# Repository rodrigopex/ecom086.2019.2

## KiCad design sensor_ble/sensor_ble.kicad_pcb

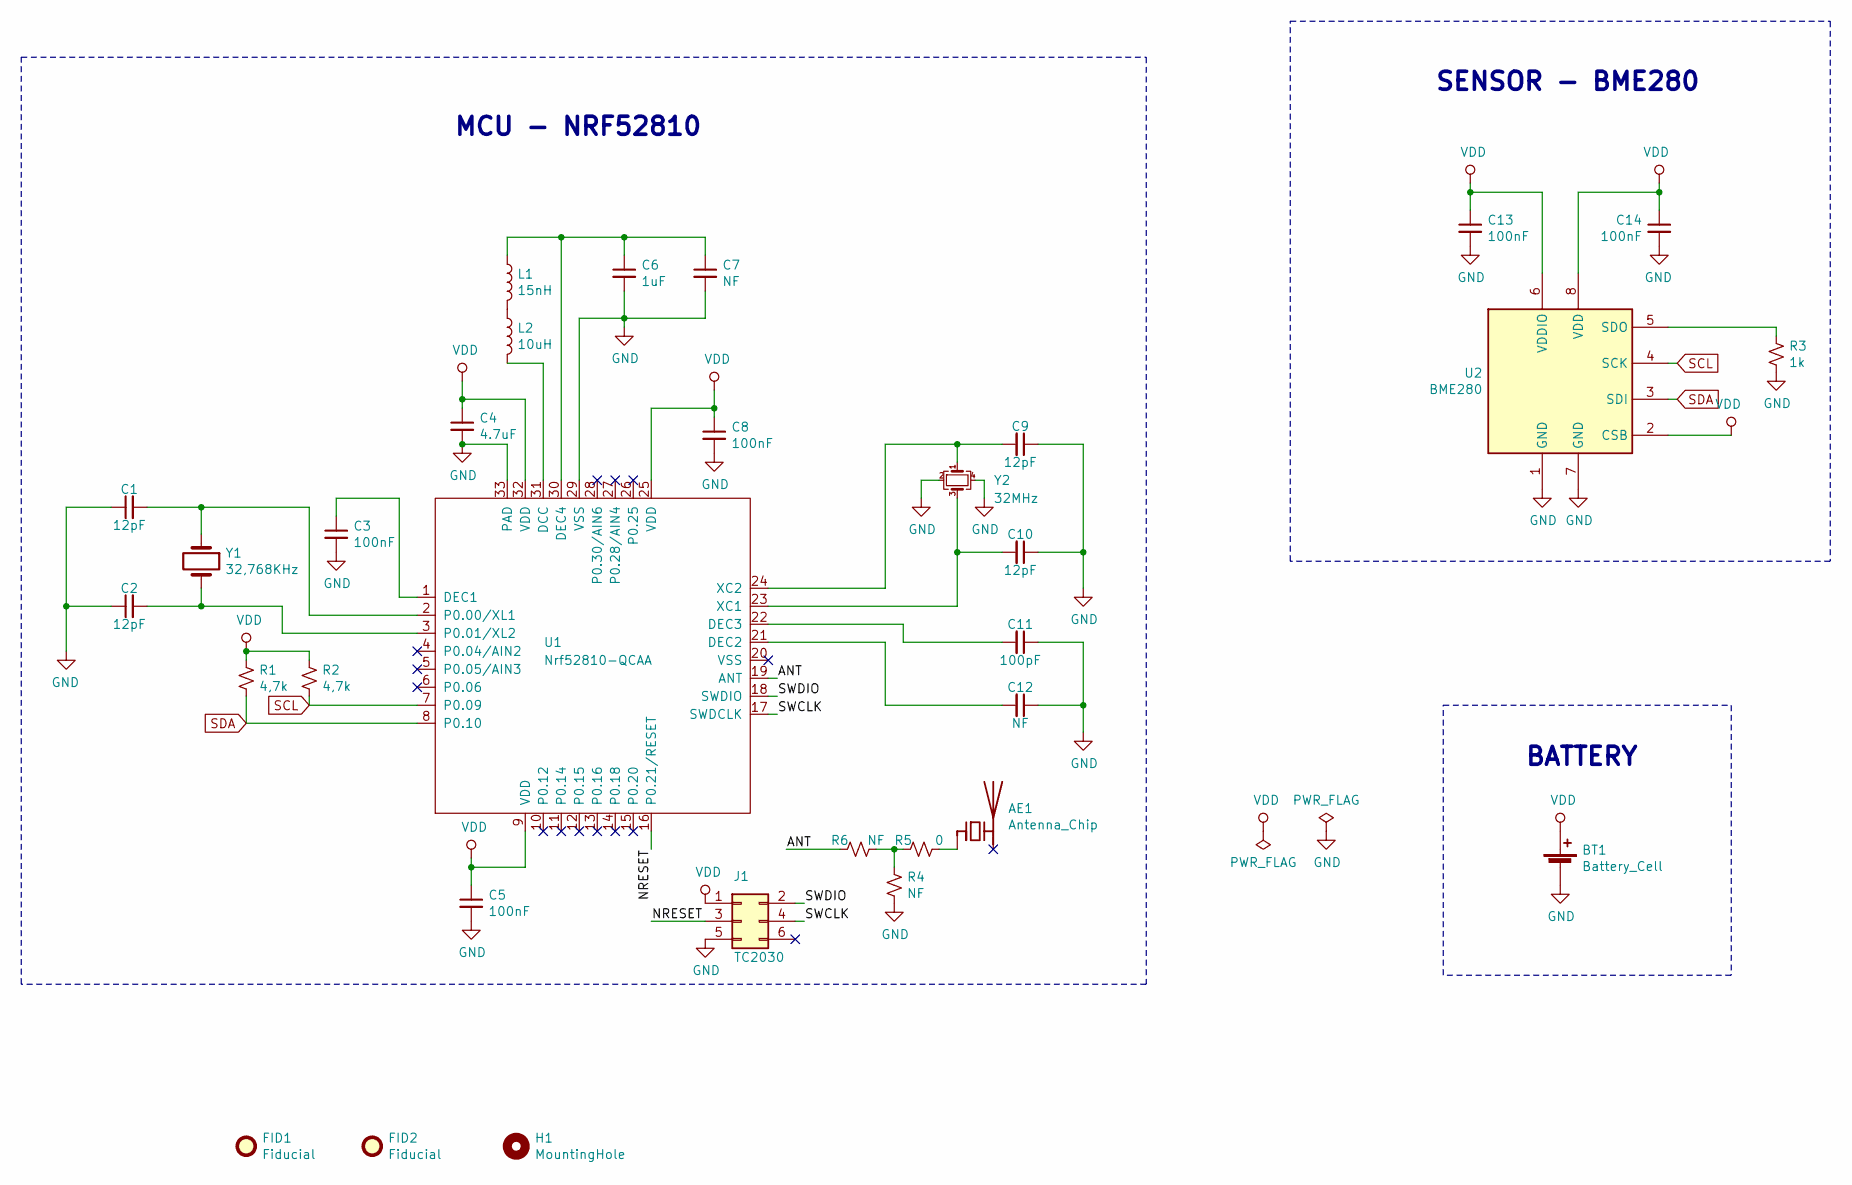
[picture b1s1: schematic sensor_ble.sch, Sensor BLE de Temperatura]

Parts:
AE1: Antenna_Chip; 2450AT18B100
BT1: Battery_Cell; Battery_Panasonic_CR2032-VS1N_Vertical_CircularHoles
C1, C2, C10: 12pF; C_0402_1005Metric
C3, C5, C14: 100nF; C_0402_1005Metric; Part Number GCM155L8EH104KE07D
C4: 4.7uF; C_0402_1005Metric
C6: 1uF; C_0402_1005Metric
C7, C12: NF; C_0402_1005Metric
C8, C13: 100nF; C_0402_1005Metric
C9: 12pF; C_0402_1005Metric; Part Number CC0402GRNPO9BN120
C11: 100pF; C_0402_1005Metric
FID1, FID2: Fiducial; Fiducial_0.5mm_Mask1.5mm
H1: MountingHole; MountingHole_2mm
J1: TC2030; Tag-Connect_TC2030-IDC-NL_2x03_P1.27mm_Vertical
L1: 15nH; L_0402_1005Metric
L2: 10uH; L_0805_2012Metric
R1, R2: 4,7k; R_0402_1005Metric
R3: 1k; R_0402_1005Metric
R4, R6: NF; R_0402_1005Metric
R5: 0; R_0402_1005Metric
U1: Nrf52810-QCAA; QFN-32-1EP_5x5mm_P0.5mm_EP3.6x3.6mm
U2: BME280; Bosch_LGA-8_2.5x2.5mm_P0.65mm_ClockwisePinNumbering
Y1: 32,768KHz; Crystal_SMD_3215-2Pin_3.2x1.5mm
Y2: 32MHz; Crystal_SMD_2016-4Pin_2.0x1.6mm

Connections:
/ANT: R6.2, U1.19 (ANT)
/NRESET: J1.3, U1.16 (P0.21/RESET)
/SWCLK: J1.4, U1.17 (SWDCLK)
/SWDIO: J1.2, U1.18 (SWDIO)
GND: BT1.2 (-), C1.1, C2.1, C3.2, C4.2, C5.2, C6.2, C7.2, C8.2, C9.1, C10.1, C11.1, C12.1, C13.2, C14.2, J1.5, R3.2, R4.1, U1.29 (VSS), U1.33 (PAD), U2.1 (GND), U2.7 (GND), Y2.2, Y2.4
unnamed: AE1.1 (FEED), R5.1
unnamed: C1.2, U1.2 (P0.00/XL1), Y1.1
unnamed: C2.2, U1.3 (P0.01/XL2), Y1.2
unnamed: C3.1, U1.1 (DEC1)
unnamed: C6.1, C7.1, L1.1, U1.30 (DEC4)
unnamed: C9.2, U1.24 (XC2), Y2.1
unnamed: C10.2, U1.23 (XC1), Y2.3
unnamed: C11.2, U1.22 (DEC3)
unnamed: C12.2, U1.21 (DEC2)
unnamed: L1.2, L2.1
unnamed: L2.2, U1.31 (DCC)
unnamed: R3.1, U2.5 (SDO)
unnamed: R4.2, R5.2, R6.1
SCL: R2.2, U1.7 (P0.09), U2.4 (SCK)
SDA: R1.2, U1.8 (P0.10), U2.3 (SDI)
VDD: BT1.1 (+), C4.1, C5.1, C8.1, C13.1, C14.1, J1.1, R1.1, R2.1, U1.9 (VDD), U1.25 (VDD), U1.32 (VDD), U2.2 (CSB), U2.6 (VDDIO), U2.8 (VDD)

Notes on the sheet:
SENSOR - BME280
BATTERY
MCU - NRF52810

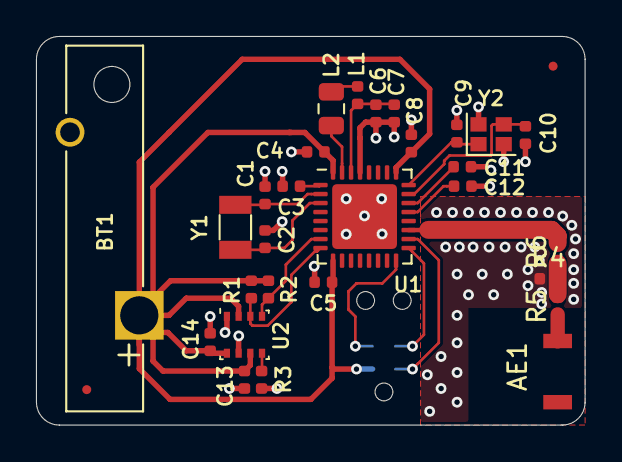
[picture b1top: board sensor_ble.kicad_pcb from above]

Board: 2 copper layers, 30.5 x 21.6 mm, 32 parts (1 on the bottom side), 21 nets.

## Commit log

2019-11-08 Projeto do sensor bluetooth de temp. pre. umi.
2019-11-22 Projeto roteado, falta a antena
2019-11-29 Adiciona antena
2020-02-03 Últimas mudanças
